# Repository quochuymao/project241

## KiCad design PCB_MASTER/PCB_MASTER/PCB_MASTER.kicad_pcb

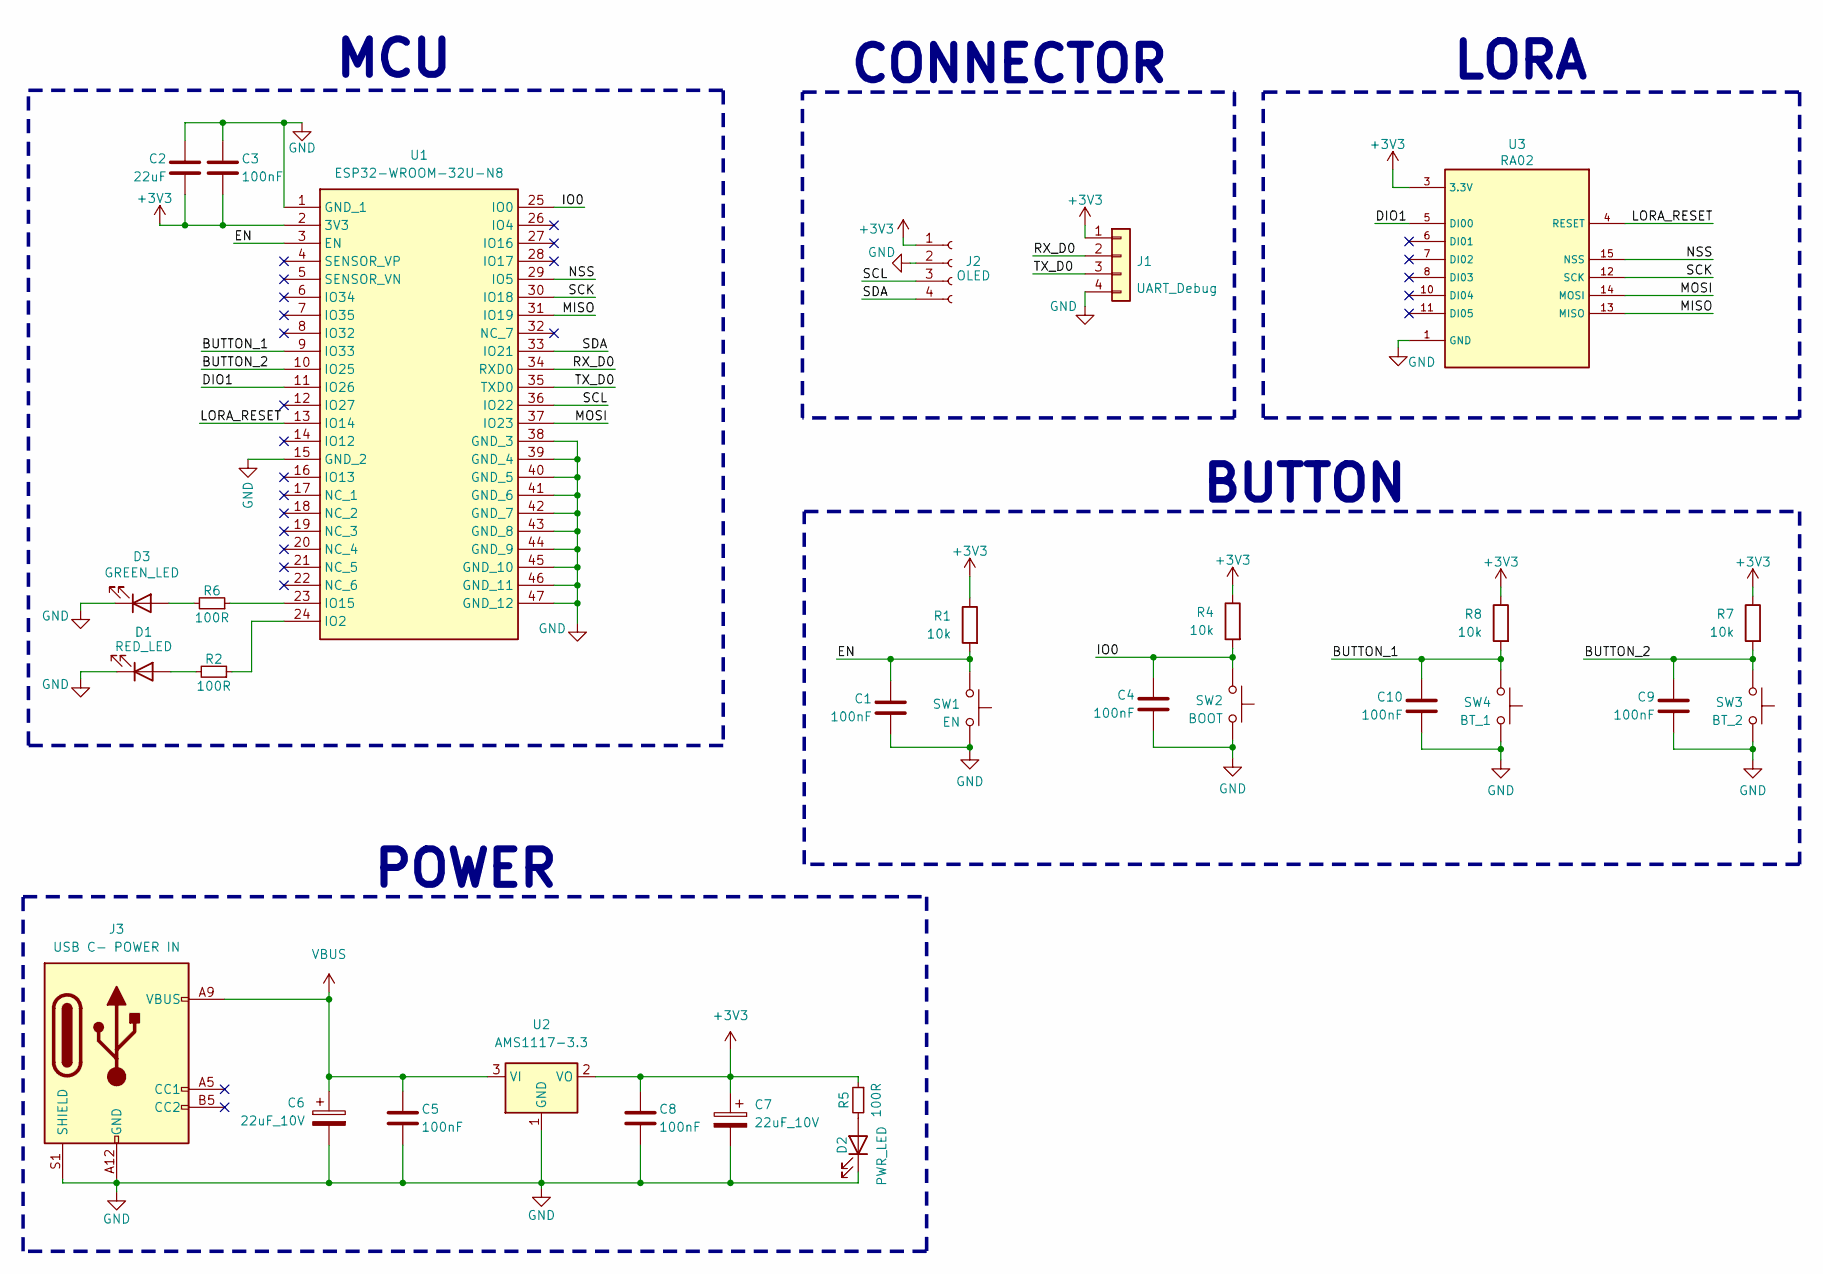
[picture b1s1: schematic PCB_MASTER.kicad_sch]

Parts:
C1, C3, C4, C9, C10: 100nF; C_0603_1608Metric; DigiKey Part Number 1276-1013-2-ND
C2: 22uF; C_0603_1608Metric; DigiKey Part Number 1276-1013-2-ND
C5, C8: 100nF; C_0603_1608Metric
C6, C7: 22uF_10V; CP_EIA-3216-10_Kemet-I
D1: RED_LED; LED_0603_1608Metric; DigiKey Part Number 732-4978-2-ND
D2: PWR_LED; LED_0603_1608Metric
D3: GREEN_LED; LED_0603_1608Metric; DigiKey Part Number 732-4978-2-ND
J1: UART_Debug; PinHeader_1x04_P2.54mm_Vertical
J2: OLED; OLED_CONN
J3: USB C- POWER IN; USB_C_Receptacle_GCT_USB4125-xx-x-0190_6P_TopMnt_Horizontal
R1, R4, R7, R8: 10k; R_0603_1608Metric; DigiKey Part Number 311-10.0KHRTR-ND
R2, R6: 100R; R_0603_1608Metric; DigiKey Part Number 311-150HRTR-ND
R5: 100R; R_0603_1608Metric
SW1: EN; SW; DigiKey Part Number CKN10502TR-ND
SW2: BOOT; SW; DigiKey Part Number CKN10502TR-ND
SW3: BT_2; SW; DigiKey Part Number CKN10502TR-ND
SW4: BT_1; SW; DigiKey Part Number CKN10502TR-ND
U1: ESP32-WROOM-32U-N8; ESP32WROOM32UEN8
U2: AMS1117-3.3; SOT-223-3_TabPin2
U3: RA02; RA-02

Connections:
+3V3: C2.2, C3.2, C7.1, C8.1, J1.1, J2.1, R1.1, R4.1, R5.1, R7.1, R8.1, U1.2 (3V3), U2.2 (VO), U3.3 (3.3V)
/BUTTON_1: C10.1, R8.2, SW4.2, U1.9 (IO33)
/BUTTON_2: C9.1, R7.2, SW3.2, U1.10 (IO25)
/DIO1: U1.11 (IO26), U3.5 (DI00)
/EN: C1.1, R1.2, SW1.2, U1.3 (EN)
/IO0: C4.1, R4.2, SW2.2, U1.25 (IO0)
/LORA_RESET: U1.13 (IO14), U3.4 (RESET)
/MISO: U1.31 (IO19), U3.13 (MISO)
/MOSI: U1.37 (IO23), U3.14 (MOSI)
/NSS: U1.29 (IO5), U3.15 (NSS)
/RX_D0: J1.2, U1.34 (RXD0)
/SCK: U1.30 (IO18), U3.12 (SCK)
/SCL: J2.3, U1.36 (IO22)
/SDA: J2.4, U1.33 (IO21)
/TX_D0: J1.3, U1.35 (TXD0)
GND: C1.2, C2.1, C3.1, C4.2, C5.2, C6.2, C7.2, C8.2, C9.2, C10.2, D1.1 (K), D2.1 (K), D3.1 (K), J1.4, J2.2, J3.A12 (GND), J3.B12 (GND), J3.S1 (SHIELD), SW1.1, SW2.1, SW3.1, SW4.1, U1.1 (GND_1), U1.15 (GND_2), U1.38 (GND_3), U1.39 (GND_4), U1.40 (GND_5), U1.41 (GND_6), U1.42 (GND_7), U1.43 (GND_8), U1.44 (GND_9), U1.45 (GND_10), U1.46 (GND_11), U1.47 (GND_12), U2.1 (GND), U3.1 (GND), U3.2 (GND), U3.9 (GND), U3.16 (GND)
unnamed: D1.2 (A), R2.2
unnamed: D2.2 (A), R5.2
unnamed: D3.2 (A), R6.2
unnamed: R2.1, U1.24 (IO2)
unnamed: R6.1, U1.23 (IO15)
VBUS: C5.1, C6.1, J3.A9 (VBUS), J3.B9 (VBUS), U2.3 (VI)

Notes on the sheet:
MCU
BUTTON
POWER
LORA
CONNECTOR

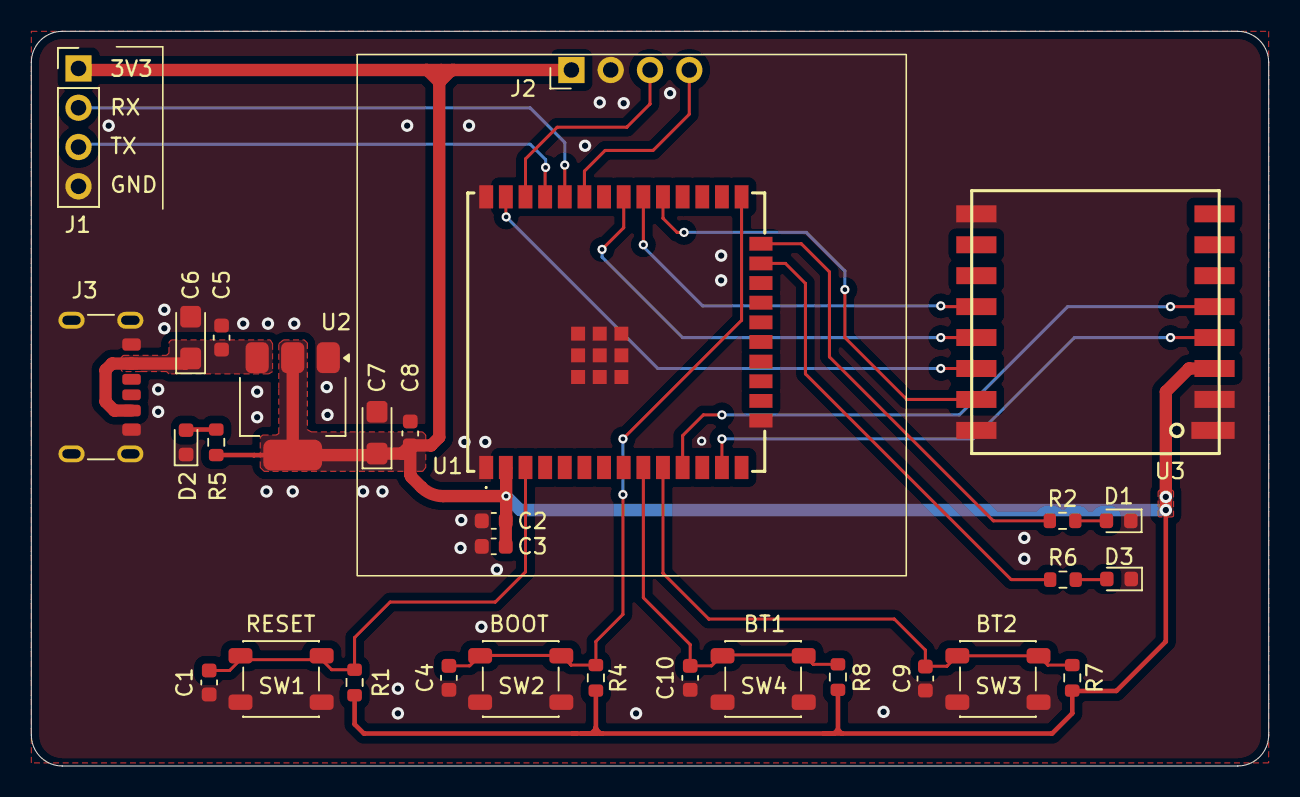
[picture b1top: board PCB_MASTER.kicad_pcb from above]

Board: 2 copper layers, 80.0 x 47.5 mm, 30 parts (0 on the bottom side), 22 nets.

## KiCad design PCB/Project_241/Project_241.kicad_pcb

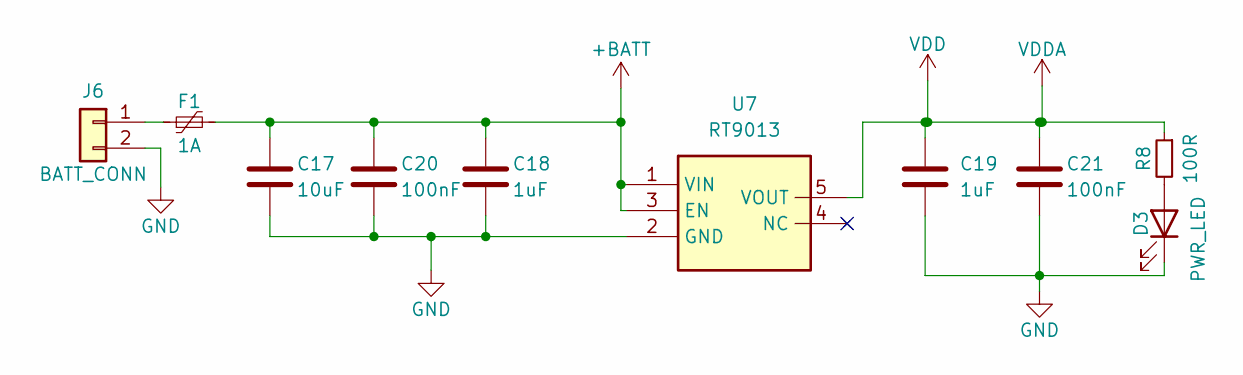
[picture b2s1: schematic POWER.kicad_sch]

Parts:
C17: 10uF; C_0603_1608Metric
C18, C19: 1uF; C_0603_1608Metric
C20, C21: 100nF; C_0603_1608Metric
D3: PWR_LED; LED_0603_1608Metric
F1: 1A; Fuse_0805_2012Metric
J6: BATT_CONN; XH 2.54 2Pin Female
R8: 100R; R_0603_1608Metric
U7: RT9013; SOT23_5

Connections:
+BATT: C17.1, C18.1, C20.1, F1.2, U7.1 (VIN), U7.3 (EN)
GND: C17.2, C18.2, C19.2, C20.2, C21.2, D3.1 (K), J6.2, U7.2 (GND); also elsewhere on the board
unnamed: D3.2 (A), R8.2
unnamed: F1.1, J6.1
VDD: C19.1, C21.1, R8.1, U7.5 (VOUT); also elsewhere on the board

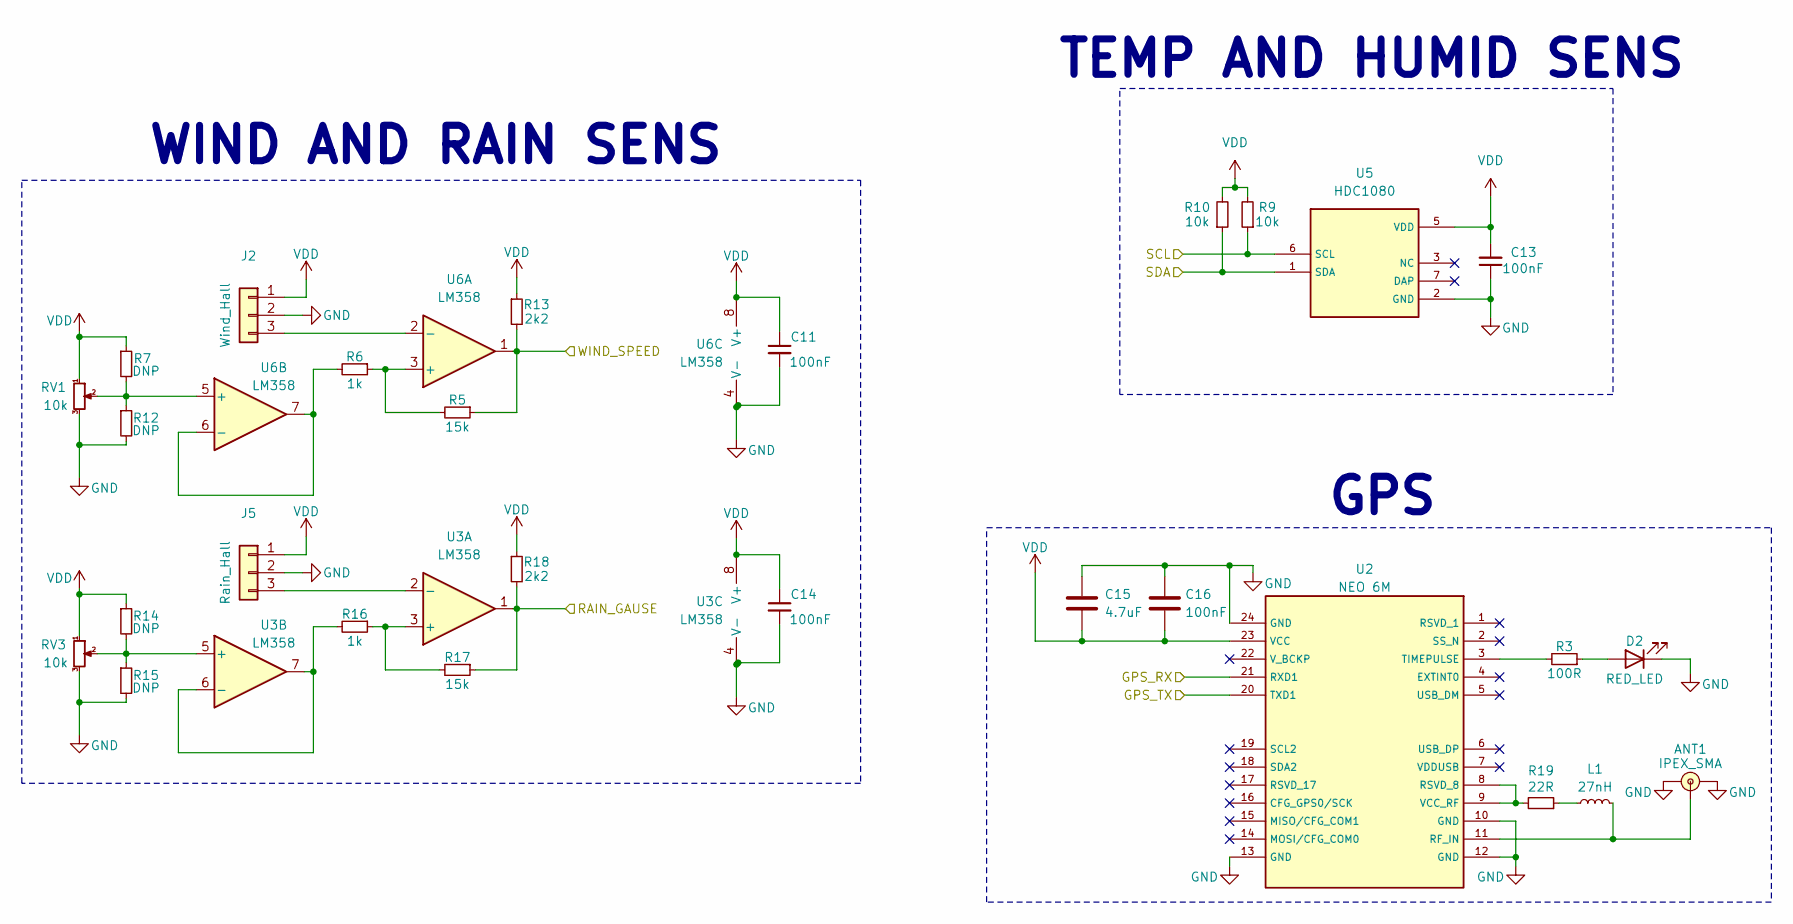
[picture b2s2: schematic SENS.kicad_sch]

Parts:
ANT1: IPEX_SMA; ANT_SMA_3PIN
C11, C13, C14, C16: 100nF; C_0603_1608Metric
C15: 4.7uF; C_0603_1608Metric
D2: RED_LED; LED_0603_1608Metric
J2: Wind_Hall; XH_3P_2.54mm_Vertical
J5: Rain_Hall; XH_3P_2.54mm_Vertical
L1: 27nH; L_0603_1608Metric
R3: 100R; R_0603_1608Metric
R5, R17: 15k; R_0603_1608Metric
R6, R16: 1k; R_0603_1608Metric
R7, R12, R14, R15: DNP; R_0603_1608Metric
R9, R10: 10k; R_0603_1608Metric
R13, R18: 2k2; R_0603_1608Metric
R19: 22R; R_0603_1608Metric
RV1, RV3: 10k; Poten_3PIN_SMD
U2: NEO 6M; XCVR_NEO-6M-GPS
U3, U6: LM358; SOIC-8
U5: HDC1080; SON100P300X300X80-7N

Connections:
/MCU/GPS_RX: U2.21 (RXD1); also elsewhere on the board
/MCU/GPS_TX: U2.20 (TXD1); also elsewhere on the board
/MCU/RAIN_GAUSE: R17.1, R18.2, U3.1; also elsewhere on the board
/MCU/SCL: R9.1, U5.6 (SCL); also elsewhere on the board
/MCU/SDA: R10.1, U5.1 (SDA); also elsewhere on the board
/MCU/WIND_SPEED: R5.1, R13.2, U6.1; also elsewhere on the board
GND: ANT1.2 (GND), ANT1.3 (GND), C11.2, C13.1, C14.2, C15.1, C16.1, D2.1 (K), J2.2, J5.2, R12.2, R15.2, RV1.3, RV3.3, U2.10 (GND), U2.12 (GND), U2.13 (GND), U2.24 (GND), U3.4 (V-), U5.2 (GND), U6.4 (V-); also elsewhere on the board
unnamed: ANT1.1 (FEED), L1.2, U2.11 (RF_IN)
unnamed: D2.2 (A), R3.1
unnamed: J2.3, U6.2 (-)
unnamed: J5.3, U3.2 (-)
unnamed: L1.1, R19.1
unnamed: R19.2, U2.8 (RSVD_8), U2.9 (VCC_RF)
unnamed: R3.2, U2.3 (TIMEPULSE)
unnamed: R16.1, R17.2, U3.3 (+)
unnamed 36: R14.2, R15.1, RV3.2, U3.5 (+); also elsewhere on the board
unnamed: R16.2, U3.6 (-), U3.7
unnamed: R5.2, R6.1, U6.3 (+)
unnamed: R7.2, R12.1, RV1.2, U6.5 (+)
unnamed: R6.2, U6.6 (-), U6.7
VDD: C11.1, C13.2, C14.1, C15.2, C16.2, J2.1, J5.1, R7.1, R9.2, R10.2, R13.1, R14.1, R18.1, RV1.1, RV3.1, U2.23 (VCC), U3.8 (V+), U5.5 (VDD), U6.8 (V+); also elsewhere on the board

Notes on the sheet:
TEMP AND HUMID SENS
GPS
WIND AND RAIN SENS

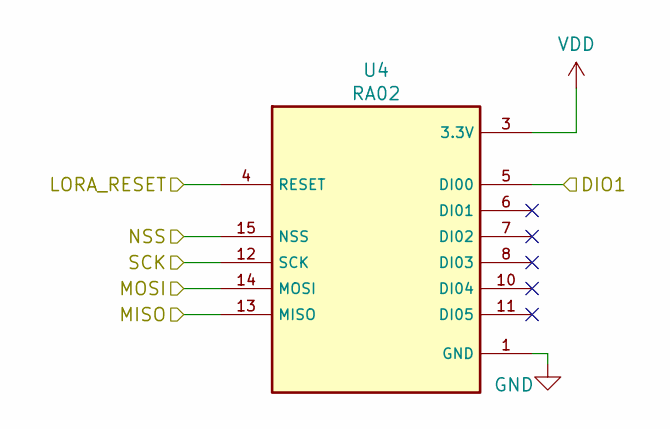
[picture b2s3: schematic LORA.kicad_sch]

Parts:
U4: RA02; RA-02

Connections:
/LORA/DIO1: U4.5 (DI00); also elsewhere on the board
/LORA/LORA_RESET: U4.4 (RESET); also elsewhere on the board
/LORA/MISO: U4.13 (MISO); also elsewhere on the board
/LORA/MOSI: U4.14 (MOSI); also elsewhere on the board
/LORA/NSS: U4.15 (NSS); also elsewhere on the board
/LORA/SCK: U4.12 (SCK); also elsewhere on the board
GND: U4.1 (GND), U4.2 (GND), U4.9 (GND), U4.16 (GND); also elsewhere on the board
VDD: U4.3 (3.3V); also elsewhere on the board

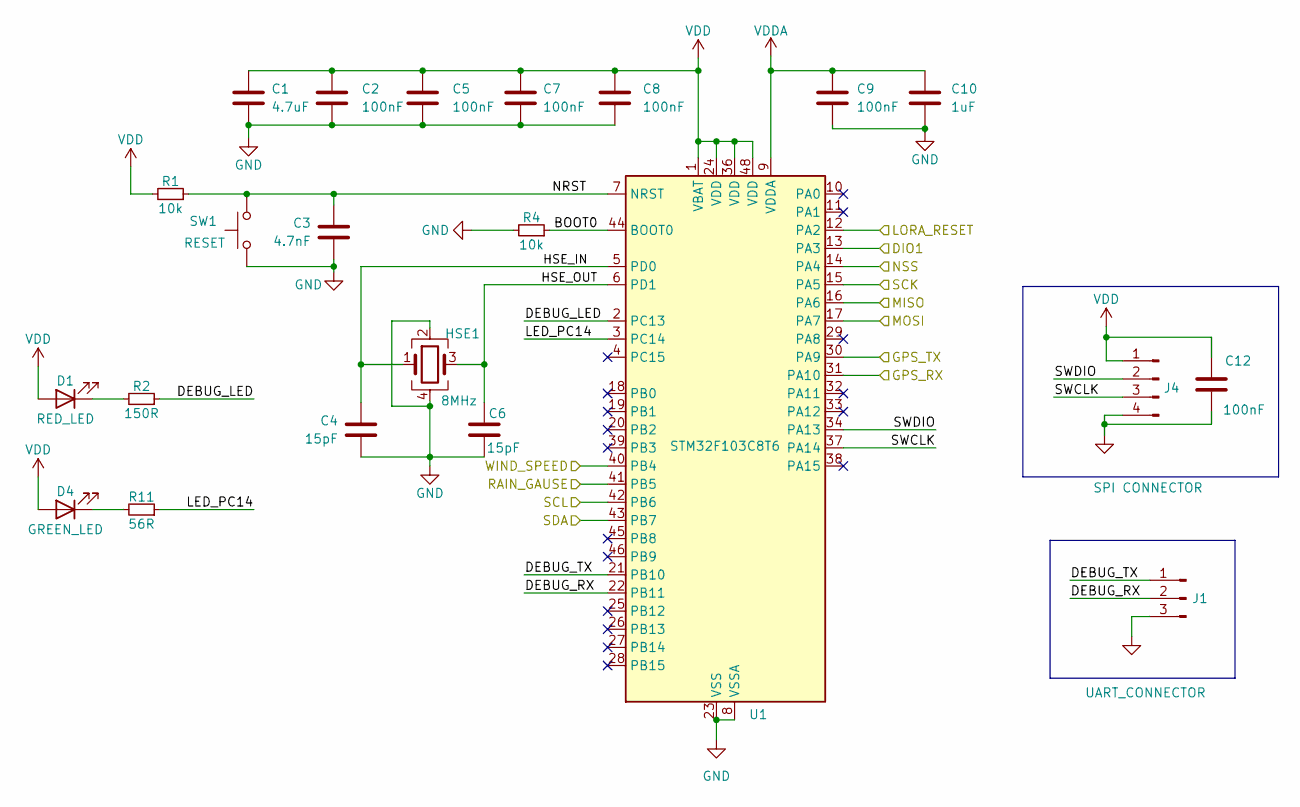
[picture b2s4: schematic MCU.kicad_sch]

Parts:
C1: 4.7uF; C_0603_1608Metric
C2, C5, C7, C8, C9, C12: 100nF; C_0603_1608Metric
C3: 4.7nF; C_0603_1608Metric
C4, C6: 15pF; C_0603_1608Metric
C10: 1uF; C_0603_1608Metric
D1: RED_LED; LED_0603_1608Metric
D4: GREEN_LED; LED_0603_1608Metric
HSE1: 8MHz; Crystal_SMD_3225-4Pin_3.2x2.5mm
J1: UART_CONNECTOR; PinHeader_1x03_P2.54mm_Vertical
J4: SPI CONNECTOR; PinHeader_1x04_P2.54mm_Vertical
R1, R4: 10k; R_0603_1608Metric
R2: 150R; R_0603_1608Metric
R11: 56R; R_0603_1608Metric
SW1: RESET; SW_SPST_PTS647_Sx38
U1: STM32F103C8T6; LQFP-48_7x7mm_P0.5mm

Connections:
/LORA/DIO1: U1.13 (PA3); also elsewhere on the board
/LORA/LORA_RESET: U1.12 (PA2); also elsewhere on the board
/LORA/MISO: U1.16 (PA6); also elsewhere on the board
/LORA/MOSI: U1.17 (PA7); also elsewhere on the board
/LORA/NSS: U1.14 (PA4); also elsewhere on the board
/LORA/SCK: U1.15 (PA5); also elsewhere on the board
/MCU/BOOT0: R4.1, U1.44 (BOOT0)
/MCU/DEBUG_LED: R2.1, U1.2 (PC13)
/MCU/DEBUG_RX: J1.2, U1.22 (PB11)
/MCU/DEBUG_TX: J1.1, U1.21 (PB10)
/MCU/GPS_RX: U1.31 (PA10); also elsewhere on the board
/MCU/GPS_TX: U1.30 (PA9); also elsewhere on the board
/MCU/HSE_IN: C4.1, HSE1.1, U1.5 (PD0)
/MCU/HSE_OUT: C6.1, HSE1.3, U1.6 (PD1)
/MCU/LED_PC14: R11.1, U1.3 (PC14)
/MCU/NRST: C3.1, R1.1, SW1.2, U1.7 (NRST)
/MCU/RAIN_GAUSE: U1.41 (PB5); also elsewhere on the board
/MCU/SCL: U1.42 (PB6); also elsewhere on the board
/MCU/SDA: U1.43 (PB7); also elsewhere on the board
/MCU/SWCLK: J4.3, U1.37 (PA14)
/MCU/SWDIO: J4.2, U1.34 (PA13)
/MCU/WIND_SPEED: U1.40 (PB4); also elsewhere on the board
GND: C1.2, C2.2, C3.2, C4.2, C5.2, C6.2, C7.2, C8.2, C9.2, C10.2, C12.2, HSE1.2, HSE1.4, J1.3, J4.4, R4.2, SW1.1, U1.8 (VSSA), U1.23 (VSS), U1.35 (VSS), U1.47 (VSS); also elsewhere on the board
unnamed: D1.1 (K), R2.2
unnamed: D4.1 (K), R11.2
VDD: C1.1, C2.1, C5.1, C7.1, C8.1, C9.1, C10.1, C12.1, D1.2 (A), D4.2 (A), J4.1, R1.2, U1.1 (VBAT), U1.9 (VDDA), U1.24 (VDD), U1.36 (VDD), U1.48 (VDD); also elsewhere on the board

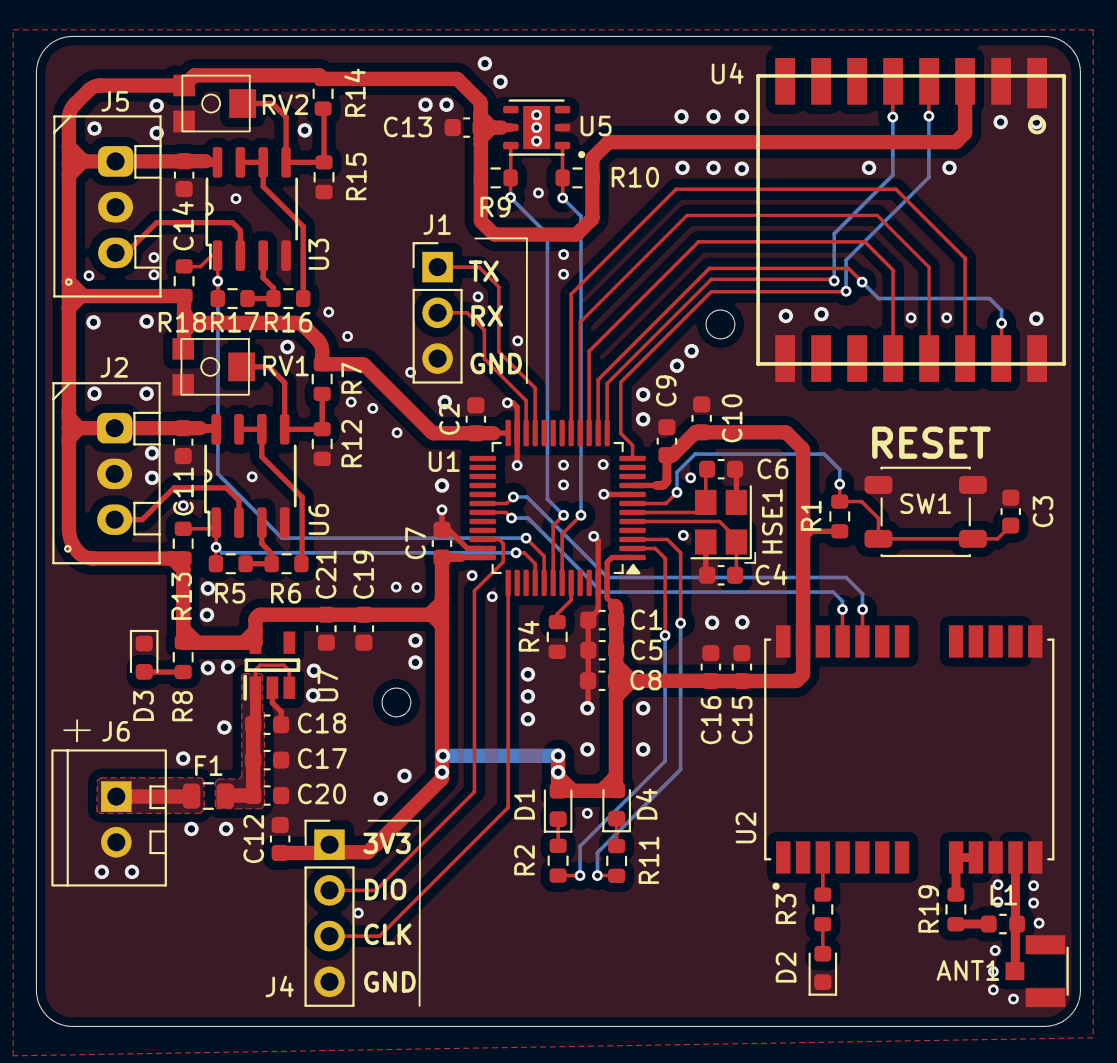
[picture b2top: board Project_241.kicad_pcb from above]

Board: 2 copper layers, 58.0 x 55.0 mm, 63 parts (0 on the bottom side), 42 nets.

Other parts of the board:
RV2: 10k; Poten_3PIN_SMD

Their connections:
GND: RV2.3; also elsewhere on the board
unnamed 36: RV2.2; also elsewhere on the board
VDD: RV2.1; also elsewhere on the board

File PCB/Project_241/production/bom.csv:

Designator,Footprint,Quantity,Value,LCSC Part #
ANT1,ANT_SMA_3PIN,1,IPEX_SMA,
"C1, C15",0603,2,4.7uF,
"C10, C18, C19",0603,3,1uF,
"C11, C12, C13, C14, C16, C2, C20, C21, C5, C7, C8, C9",0603,12,100nF,
C17,0603,1,10uF,
C3,0603,1,4.7nF,
"C4, C6",0603,2,15pF,
"D1, D2",0603,2,RED_LED,
D3,0603,1,PWR_LED,
D4,0603,1,GREEN_LED,
F1,0805,1,1A,
HSE1,Crystal_SMD_3225-4Pin_3.2x2.5mm,1,8MHz,
J2,XH_3P_2.54mm_Vertical,1,Wind_Hall,
J4,PinHeader_1x04_P2.54mm_Vertical,1,SPI CONNECTOR,
J5,XH_3P_2.54mm_Vertical,1,Rain_Hall,
J6,XH 2.54 2Pin Female,1,BATT_CONN,
L1,0603,1,27nH,
"R1, R10, R4, R9",0603,4,10k,
R11,0603,1,56R,
"R12, R14, R15, R7",0603,4,DNP,
"R13, R18",0603,2,2k2,
"R16, R6",0603,2,1k,
"R17, R5",0603,2,15k,
R19,0603,1,22R,
R2,0603,1,150R,
"R3, R8",0603,2,100R,
"RV1, RV3",Poten_3PIN_SMD,2,10k,
SW1,SW_SPST_PTS647_Sx38,1,RESET,
U1,LQFP-48_7x7mm_P0.5mm,1,STM32F103C8T6,
U2,XCVR_NEO-6M-GPS,1,NEO 6M,
"U3, U6",SOIC-8,2,LM358,
U4,RA-02,1,RA02,
U5,SON100P300X300X80-7N,1,HDC1080,
U7,SOT23_5,1,RT9013,

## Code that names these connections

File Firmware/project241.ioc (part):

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Mcu.Name=STM32F103C(8-B)Tx
Mcu.Package=LQFP48
Mcu.UserName=STM32F103C8Tx
PA10.GPIOParameters=GPIO_Label
PA10.GPIO_Label=GPS_RX
PA10.Mode=Asynchronous
PA10.Signal=USART1_RX
PA13.Mode=Serial_Wire
PA13.Signal=SYS_JTMS-SWDIO
PA14.Mode=Serial_Wire
PA14.Signal=SYS_JTCK-SWCLK
PA2.GPIOParameters=GPIO_Label
PA2.GPIO_Label=RST
PA2.Signal=GPIO_Output
PA3.GPIOParameters=GPIO_Label,GPIO_ModeDefaultEXTI
PA3.GPIO_Label=DIO0
PA3.GPIO_ModeDefaultEXTI=GPIO_MODE_IT_FALLING
PA3.Signal=GPXTI3
PA4.GPIOParameters=GPIO_Label
PA4.GPIO_Label=NSS
PA4.Signal=GPIO_Output
PA5.Mode=Full_Duplex_Master
PA5.Signal=SPI1_SCK
PA6.Mode=Full_Duplex_Master
PA6.Signal=SPI1_MISO
PA7.Mode=Full_Duplex_Master
PA7.Signal=SPI1_MOSI
PA9.GPIOParameters=GPIO_Label
PA9.GPIO_Label=GPS_TX
PA9.Mode=Asynchronous
PA9.Signal=USART1_TX
PB10.GPIOParameters=GPIO_Label
PB10.GPIO_Label=DEBUG_TX
PB10.Mode=Asynchronous
PB10.Signal=USART3_TX
PB11.GPIOParameters=GPIO_Label
PB11.GPIO_Label=DEBUG_RX
PB11.Mode=Asynchronous
PB11.Signal=USART3_RX
PB4.GPIOParameters=GPIO_Label,GPIO_ModeDefaultEXTI
PB4.GPIO_Label=WIND
PB4.GPIO_ModeDefaultEXTI=GPIO_MODE_IT_FALLING
PB4.Signal=GPXTI4
PB5.GPIOParameters=GPIO_Label,GPIO_ModeDefaultEXTI
PB5.GPIO_Label=RAIN
PB5.GPIO_ModeDefaultEXTI=GPIO_MODE_IT_FALLING
PB5.Signal=GPXTI5
PB6.Mode=I2C
PB6.Signal=I2C1_SCL
PB7.Mode=I2C
PB7.Signal=I2C1_SDA
PC13-TAMPER-RTC.GPIOParameters=GPIO_Label
PC13-TAMPER-RTC.GPIO_Label=TEST
PC13-TAMPER-RTC.Signal=GPIO_Output
PC14-OSC32_IN.GPIOParameters=GPIO_Label
PC14-OSC32_IN.GPIO_Label=LED_PC14
PC14-OSC32_IN.Signal=GPIO_Output
PD0-OSC_IN.Mode=HSE-External-Oscillator
PD0-OSC_IN.Signal=RCC_OSC_IN
PD1-OSC_OUT.Mode=HSE-External-Oscillator
PD1-OSC_OUT.Signal=RCC_OSC_OUT
RCC.SYSCLKFreq_VALUE=48000000
RCC.SYSCLKSource=RCC_SYSCLKSOURCE_PLLCLK
board=custom

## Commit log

2024-10-21 PCB files create
2024-10-21 add firmware
2024-10-21 update pcb schematic
2024-10-22 add doc
2024-10-22 Update pcb and doc folder
2024-10-22 remove
2024-10-22 add git ignore
2024-10-25 add SPI
2024-10-25 update schematic
2024-10-27 update report
2024-11-22 update gerber
2024-12-04 update code
2024-12-31 update docs
